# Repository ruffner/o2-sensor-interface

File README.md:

# o2-sensor-interface
An unconventional use of an [automotive oxygen sensor](https://www.oreillyauto.com/detail/b/bosch-3073/engine-sensors---emissions-25132/emission-smog-parts-16465/oxygen-air-fuel-ratio-sensor-12041/24932ed2a03f/bosch-oxygen-sensor/15510/2575736)

## Assembled Board

## Software Setup
The board will emulate a USB serial com port. You can use the arduino serial monitor (Board -> Port menu). 
- [Arduino IDE 1.8.12](https://www.arduino.cc/en/main/software)

You can also use putty if on windows machine.
- [Putty](https://www.chiark.greenend.org.uk/~sgtatham/putty/latest.html)

You only need teensyduino to *update* code on the microcontroller. To simply monitor the serial output it is not needed.
- [TeensyDuino installer](https://www.pjrc.com/teensy/td_download.html)

Needed libs from the Arduino library manager
- Adafruit BusIO
- Adafruit MAX38155
- FIR Filter Arduino Library

## Schematic
Errata: 
- heater pin to mosfet should be 20 instead of 19 (for pwm capability). jumpered on board for now.
- 0.1uF cap across opamp input (grey wire). soldered on bottom of board for now.

## Layout
Dimensions in inches.

### Top Render

### Bottom Render

## Partslist

Thermocouple: [https://www.amazon.com/gp/product/B07QK4ZG1G](https://www.amazon.com/gp/product/B07QK4ZG1G)

[Digikey BOM](pcb/Digikey_Bom_8219274.csv)

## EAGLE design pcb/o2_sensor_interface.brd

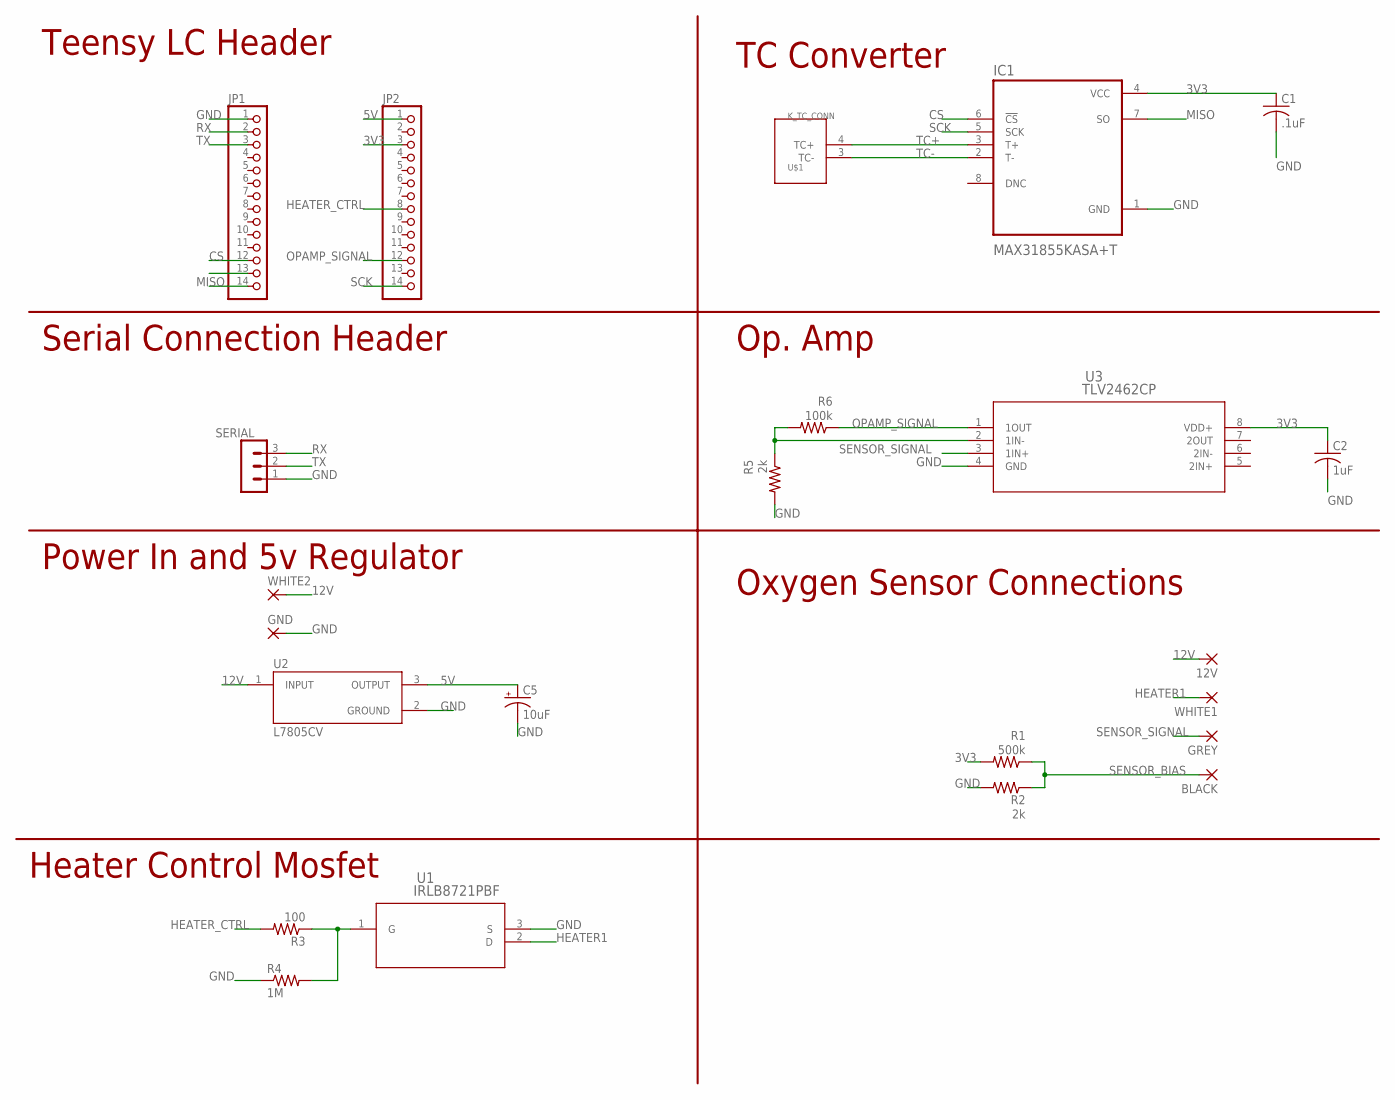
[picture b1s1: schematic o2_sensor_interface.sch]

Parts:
12V: 3,17/1,3
BLACK: 3,17/1,3
C1: .1uF; C025-030X050
C2: 1uF; C025-030X050
C5: 10uF; E2-4
GND: 3,17/1,3
GREY: 3,17/1,3
IC1: MAX31855KASA+T; SOIC127P600X175-8N
JP1, JP2: PINHD-1X14; 1X14
R1: 500k; 0207/9
R2, R5: 2k; 0207/9
R3: 100; 0207/9
R4: 1M; 0207/9
R6: 100k; 0207/9
SERIAL: MA03-1
U1: IRLB8721PBF; PG-TO220-3
U2: L7805CV; TO255P1040X460X1968-3
U3: TLV2462CP; P8
U$1: K_TC_CONN; TC_KTYPE
WHITE1, WHITE2: 3,17/1,3

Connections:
3V3: C1.1, C2.1, IC1.4 (VCC), JP2.3, R1.2, U3.8 (VDD+)
5V: C5.+, JP2.1, U2.3 (OUTPUT)
12V: 12V.1, U2.1 (INPUT), WHITE2.1
CS: IC1.6 (!CS), JP1.12
GND: C1.2, C2.2, C5.-, GND.1, IC1.1 (GND), JP1.1, R2.2, R4.1, R5.2, SERIAL.1, U1.3 (S), U2.2 (GROUND), U3.4 (GND)
HEATER1: U1.2 (D), WHITE1.1
HEATER_CTRL: JP2.8, R3.2
MISO: IC1.7 (SO), JP1.14
unnamed: R3.1, R4.2, U1.1 (G)
unnamed: R5.1, R6.2, U3.2 (1IN-)
OPAMP_SIGNAL: JP2.12, R6.1, U3.1 (1OUT)
RX: JP1.2, SERIAL.3
SCK: IC1.5 (SCK), JP2.14
SENSOR_BIAS: BLACK.1, R1.1, R2.1
SENSOR_SIGNAL: GREY.1, U3.3 (1IN+)
TC+: IC1.3 (T+), U$1.4 (TC+)
TC-: IC1.2 (T-), U$1.3 (TC-)
TX: JP1.3, SERIAL.2

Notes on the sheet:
Power In and 5v Regulator
Serial Connection Header
Oxygen Sensor Connections
Op. Amp
TC Converter
Teensy LC Header
Heater Control Mosfet

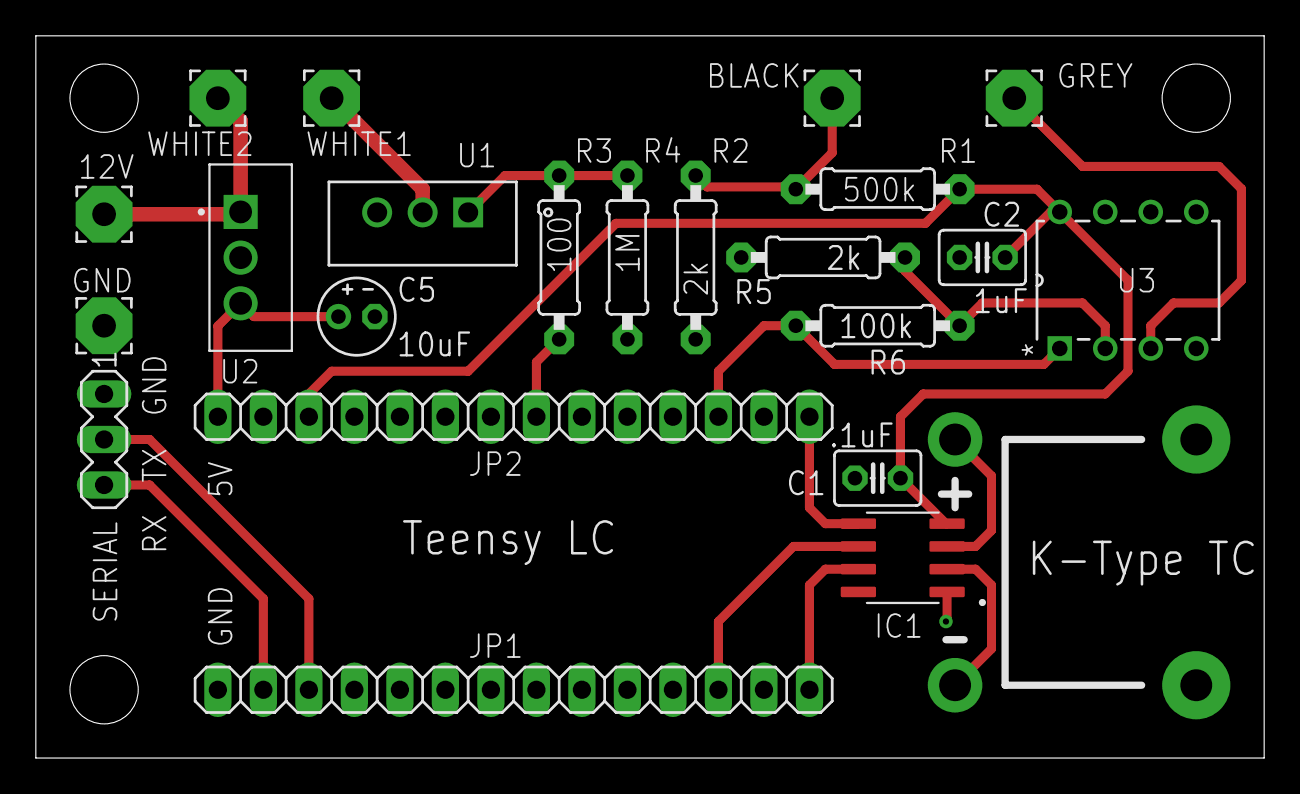
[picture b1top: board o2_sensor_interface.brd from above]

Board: 2 copper layers, 68.6 x 40.3 mm, 23 parts (0 on the bottom side), 18 nets.

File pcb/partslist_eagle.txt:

Partlist

Exported from o2_sensor_interface.sch at 4/11/20 1:49 PM

EAGLE Version 9.5.1 Copyright (c) 1988-2019 Autodesk, Inc.

Assembly variant: 

Part     Value          Device          Package               Library        Sheet

12V                     3,17/1,3        3,17/1,3              wirepad        1
BLACK                   3,17/1,3        3,17/1,3              wirepad        1
C1       .1uF           C-US025-030X050 C025-030X050          adafruit       1
C2       1uF            C-US025-030X050 C025-030X050          adafruit       1
C5       10uF           CPOL-USE2-4     E2-4                  adafruit       1
GND                     3,17/1,3        3,17/1,3              wirepad        1
GREY                    3,17/1,3        3,17/1,3              wirepad        1
IC1      MAX31855KASA+T MAX31855KASA+T  SOIC127P600X175-8N    MAX31855KASA_T 1
JP1                     PINHD-1X14      1X14                  adafruit       1
JP2                     PINHD-1X14      1X14                  adafruit       1
R1       500k           R-US_0207/9     0207/9                adafruit       1
R2       2k             R-US_0207/9     0207/9                adafruit       1
R3       100            R-US_0207/9     0207/9                adafruit       1
R4       1M             R-US_0207/9     0207/9                adafruit       1
R5       2k             R-US_0207/9     0207/9                adafruit       1
R6       100k           R-US_0207/9     0207/9                adafruit       1
SERIAL                  MA03-1          MA03-1                con-lstb       1
U$1      K_TC_CONN      K_TC_CONN       TC_KTYPE              samdg          1
U1       IRLB8721PBF    IRLB8721PBF     PG-TO220-3            samdg          1
U2       L7805CV        L7805CV         TO255P1040X460X1968-3 L7805CV        1
U3       TLV2462CP      TLV2462CP       P8                    samdg          1
WHITE1                  3,17/1,3        3,17/1,3              wirepad        1
WHITE2                  3,17/1,3        3,17/1,3              wirepad        1

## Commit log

2020-04-11 initial work on interface board.
2020-04-11 file rename
2020-04-11 updated bom to include male headers for teensy
2020-04-11 added tc connection socket
2020-04-11 add link to thermocouple in README
2020-04-11 update schematic
2020-04-12 silkscreen edit and camfile upload
2020-04-12 update thermocouple link
2020-04-20 added arduino control code and pic of assembled board
2020-04-27 test data and fixed power firmware
2020-05-05 increase sample rate to 200Hz and add 33 tap fir lowpass to output
2020-05-05 code update

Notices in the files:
parts and their libraries:
COPYRIGHT: Copyright (C) 2018 Accelerated Designs. All rights reserved
